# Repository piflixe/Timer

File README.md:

Eine Beschreibung auf deutsch findet sich in [README_GERMAN](README_GERMAN.md)

# Timer
Timer with encoder-button and relay

I built this software to control the lamp of a photo enlarger. I used a teensy LC but I guess it can run on different boards as well.

For controlling the lamp on 230V AC power, I used a solid-state relay:
http://www.segor.de/#Q=SSR2A(Modul)&M=1

Please feel free to contribute on this project. I guess there will be many things to do better since I am not a professional programmer.

# Usage
* Click: start / stop timer
* double click: turn lamp on
* long-press: switch between two timers

For a short demo, see [this video](https://drive.google.com/file/d/1NLvzjJv6i2ClzPW4vnvEkMBRsPrYZNdx/view?usp=sharing).

# Pictures

## new version (with PCB)

## old version (still hand soldered)

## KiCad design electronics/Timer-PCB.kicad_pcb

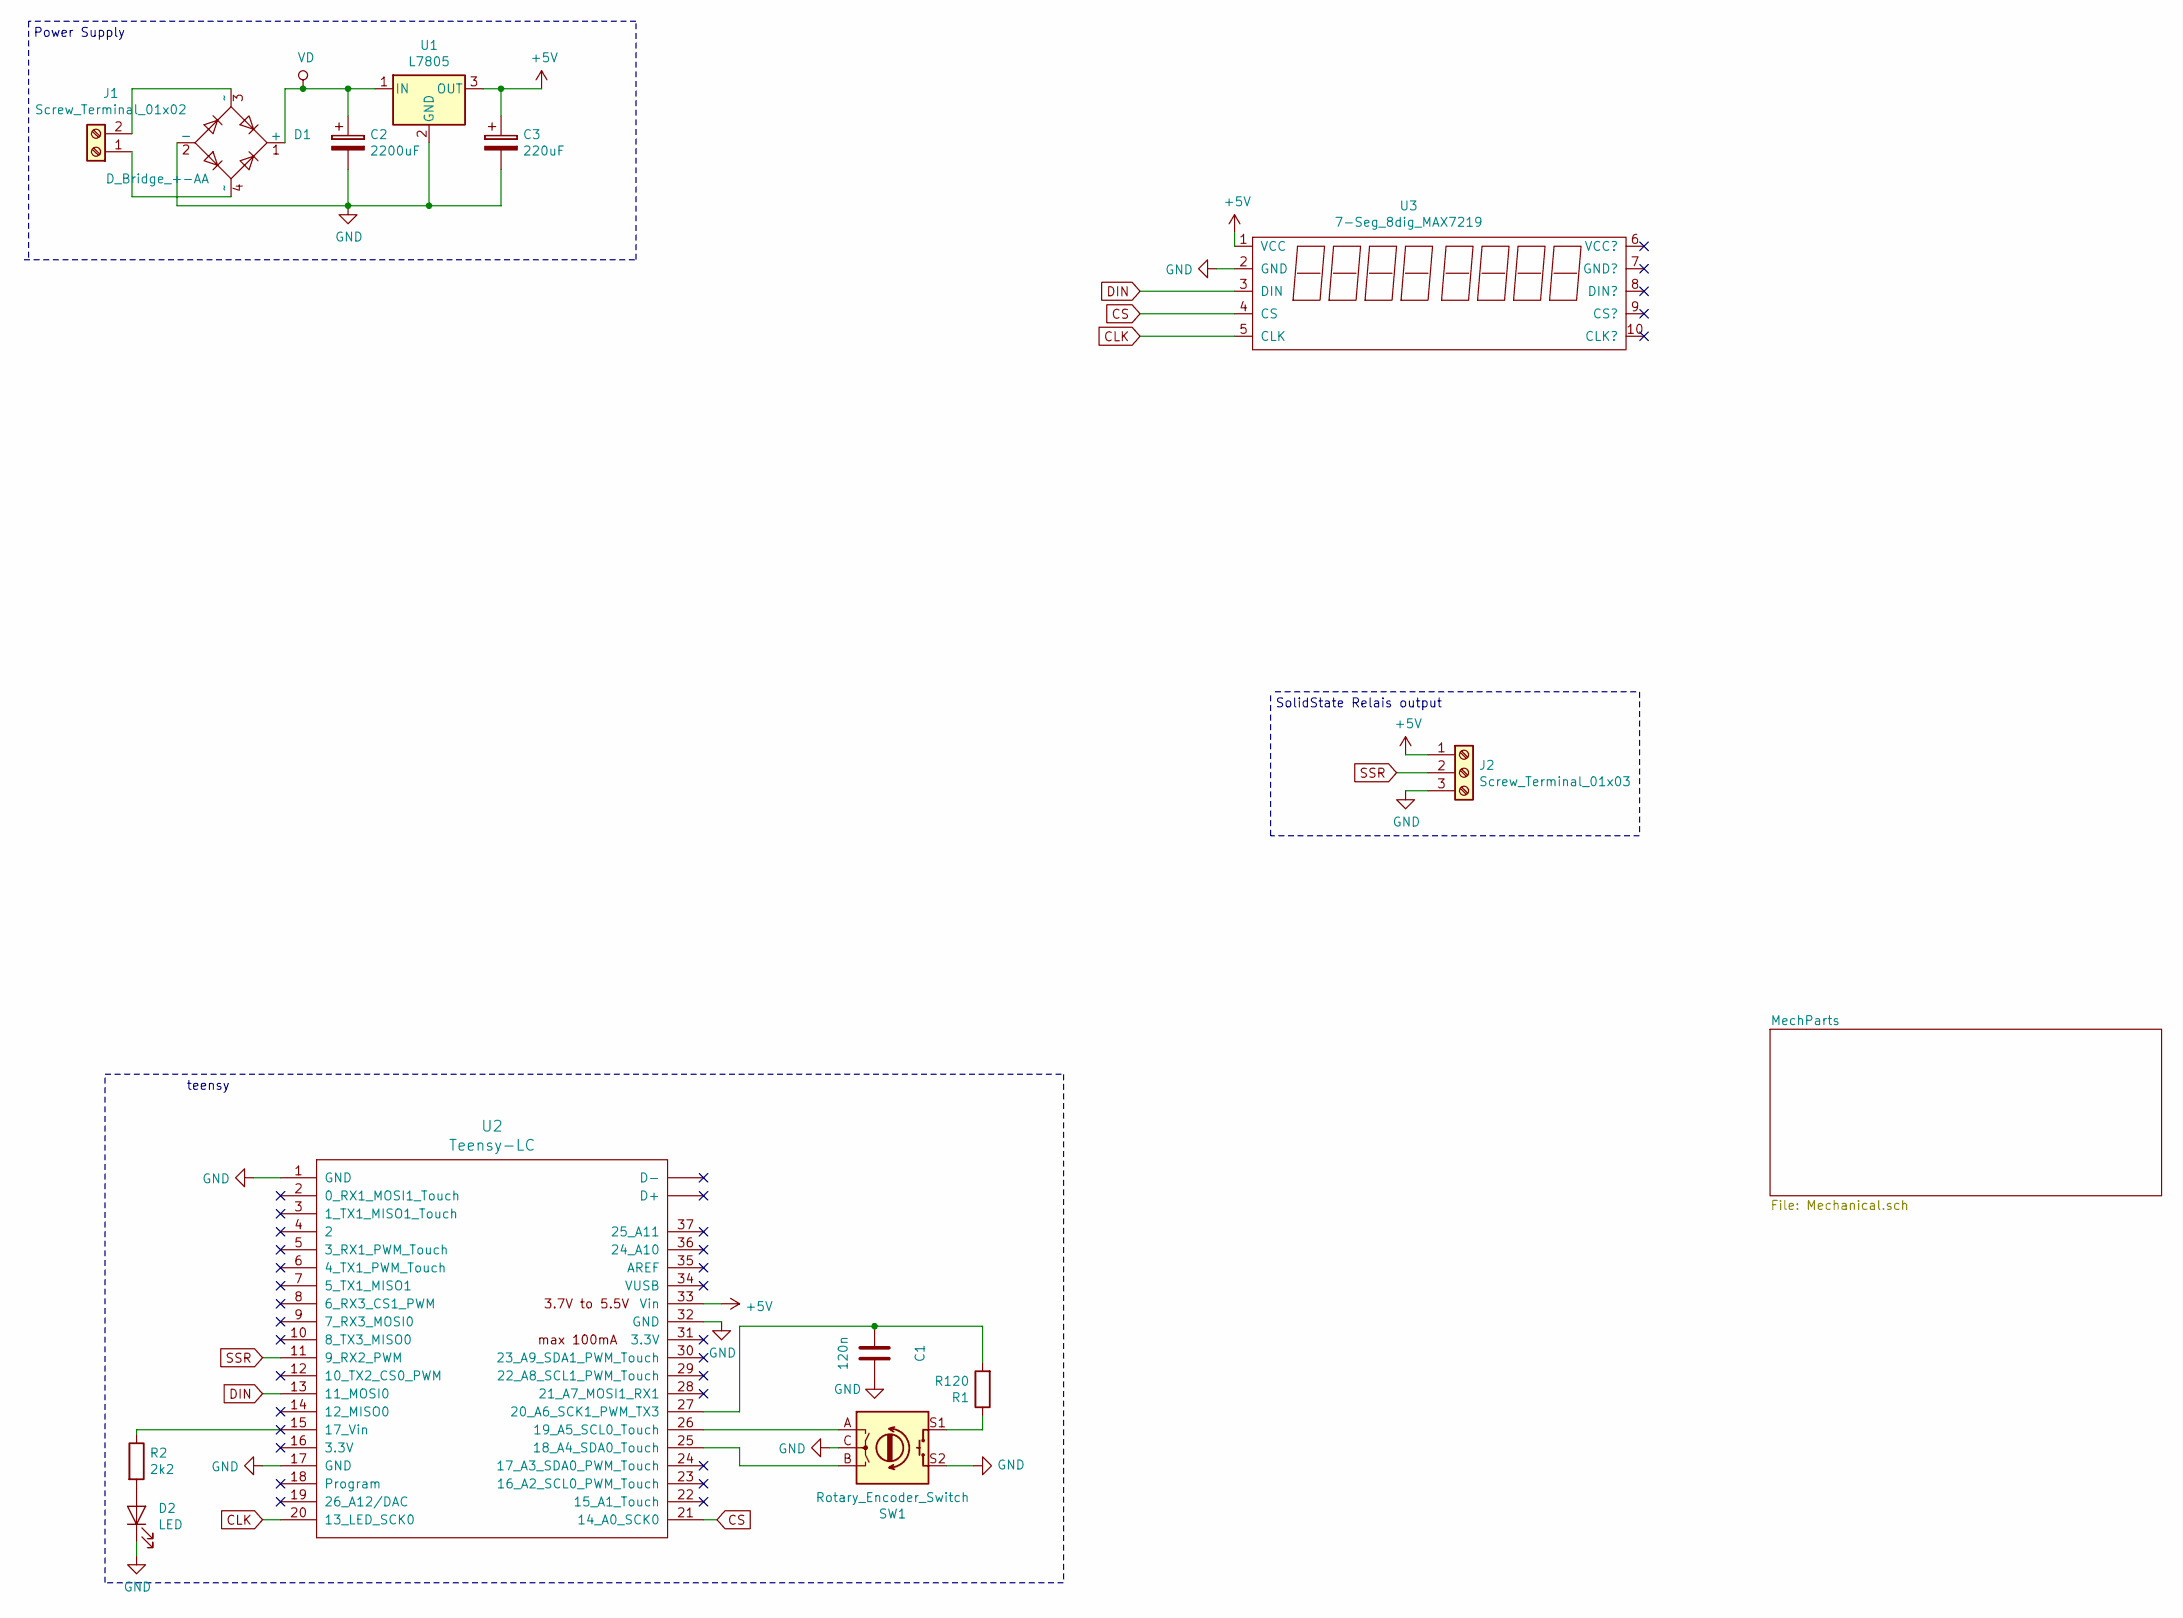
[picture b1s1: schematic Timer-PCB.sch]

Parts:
C1: 120n; C_Axial_L5.1mm_D3.1mm_P7.50mm_Horizontal_k
C2: 2200uF; CP_Radial_D13.0mm_P5.00mm_k
C3: 220uF; CP_Radial_D8.0mm_P3.50mm_k
D1: D_Bridge_+-AA; Diode_Bridge_Round_D8.9mm_k
D2: LED; LED_D5.0mm_Clear_k
J1: Screw_Terminal_01x02; TerminalBlock_Phoenix_PT-1,5-2-3.5-H_1x02_P3.50mm_Horizonta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
J2: Screw_Terminal_01x03; TerminalBlock_Phoenix_PT-1,5-3-3.5-H_1x03_P3.50mm_Horizonta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
R1: R120; R_Axial_DIN0207_L6.3mm_D2.5mm_P10.16mm_Horizontal_k
R2: 2k2; R_Axial_DIN0207_L6.3mm_D2.5mm_P10.16mm_Horizontal_k
SW1: Rotary_Encoder_Switch; RotaryEncoder_Alps_EC11E-Switch_Vertical_H20mm_CircularMoun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
U1: L7805; TO-220-3_Horizontal_TabDown_k
U2: Teensy-LC; Teensy30_31_32_LC
U3: 7-Seg_8dig_MAX7219; 7seg_8dig_MAX7219_module

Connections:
+5V: C3.1, J2.1, U1.3 (OUT), U2.33 (Vin), U3.1 (VCC)
CLK: U2.20 (13_LED_SCK0), U3.5 (CLK)
CS: U2.21 (14_A0_SCK0), U3.4 (CS)
DIN: U2.13 (11_MOSI0), U3.3 (DIN)
GND: C1.1, C2.2, C3.2, D1.2 (-), D2.1 (K), J2.3, SW1.C, SW1.S2, U1.2 (GND), U2.1 (GND), U2.17 (GND), U2.32 (GND), U3.2 (GND)
unnamed: C1.2, R1.2, U2.27 (20_A6_SCK1_PWM_TX3)
unnamed: D1.3 (~~), J1.2
unnamed: D1.4 (~~), J1.1
unnamed: D2.2 (A), R2.2
unnamed: R1.1, SW1.S1
unnamed: R2.1, U2.15 (17_Vin)
unnamed: SW1.A, U2.26 (19_A5_SCL0_Touch)
unnamed: SW1.B, U2.25 (18_A4_SDA0_Touch)
SSR: J2.2, U2.11 (9_RX2_PWM)
VD: C2.1, D1.1 (+), U1.1 (IN)

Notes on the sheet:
Power Supply
SolidState Relais output
teensy

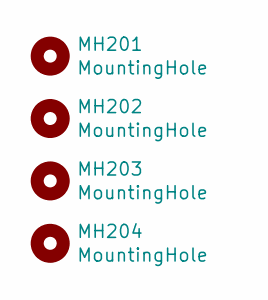
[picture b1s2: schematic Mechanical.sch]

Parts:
MH201, MH202, MH203, MH204: MountingHole; MountingHole_3.2mm_M3_DIN965_Pad_k

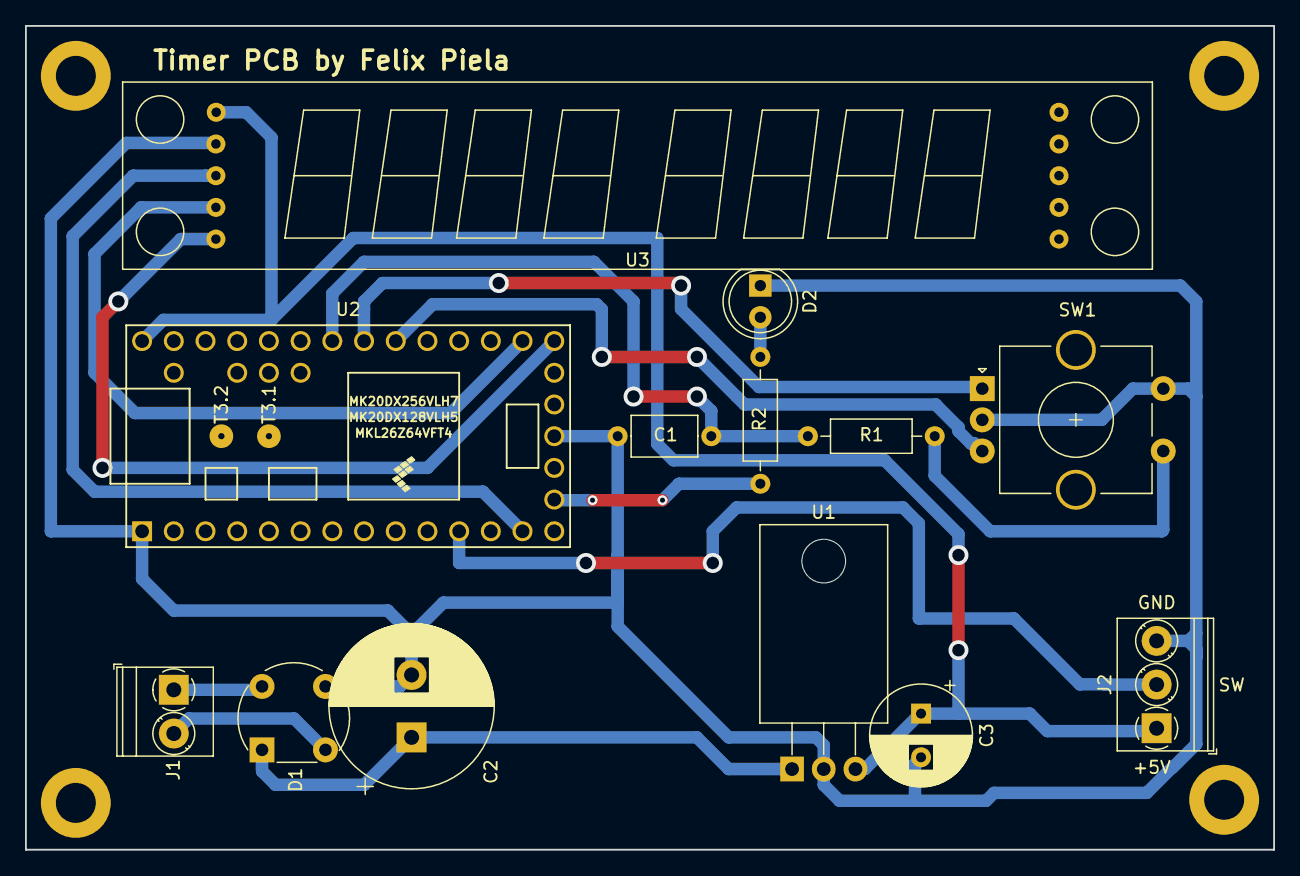
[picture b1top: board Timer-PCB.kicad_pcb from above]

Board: 2 copper layers, 100.0 x 66.0 mm, 17 parts (0 on the bottom side), 15 nets.

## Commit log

2018-02-23 - init checkin of Arduino code - completed README
2020-10-06 init kiCAD project files for PCB
2020-10-06 init first version of PCB
2020-11-03 added existing CAD files in SolidWorks format
2020-11-03 modified casing due to new parts, namely power plug with fuse and proper plug for enlarger
    still temporary and full of errors
2020-12-01 added comments for libraries to include
2020-12-01 added indicator LED feature to main loop and countdown subroutine. Layout changes still open. For details see #3
2020-12-01 updated casing for new PCB and new parts like 230V plugs. Added knob to encoder
2020-12-01 added export files and 3Dprinting files
2020-12-02 changes for improved printability
2020-12-02 added cura sliced project file and gcode
2020-12-04 made changes to casing: - Screws for PCB (easier to assemble) - casing slightly bigger (main plug didn't fit) - ribs for power transformer bigger (broke easily)
2021-01-05 introduced a boolean constant to invert the relay output to positive / negative logic
2021-01-05 added new pictures in README and README_GERMAN
2021-01-05 changed schematic to use teensy pin for indicator LED (see #3)
2021-01-05 changed symbol for display
2021-01-05 changed incorrect footprints (see #1)
2021-01-05 description on J2, see #2
2021-01-05 thermal relieves improved, see #4, ground planes redrawn
